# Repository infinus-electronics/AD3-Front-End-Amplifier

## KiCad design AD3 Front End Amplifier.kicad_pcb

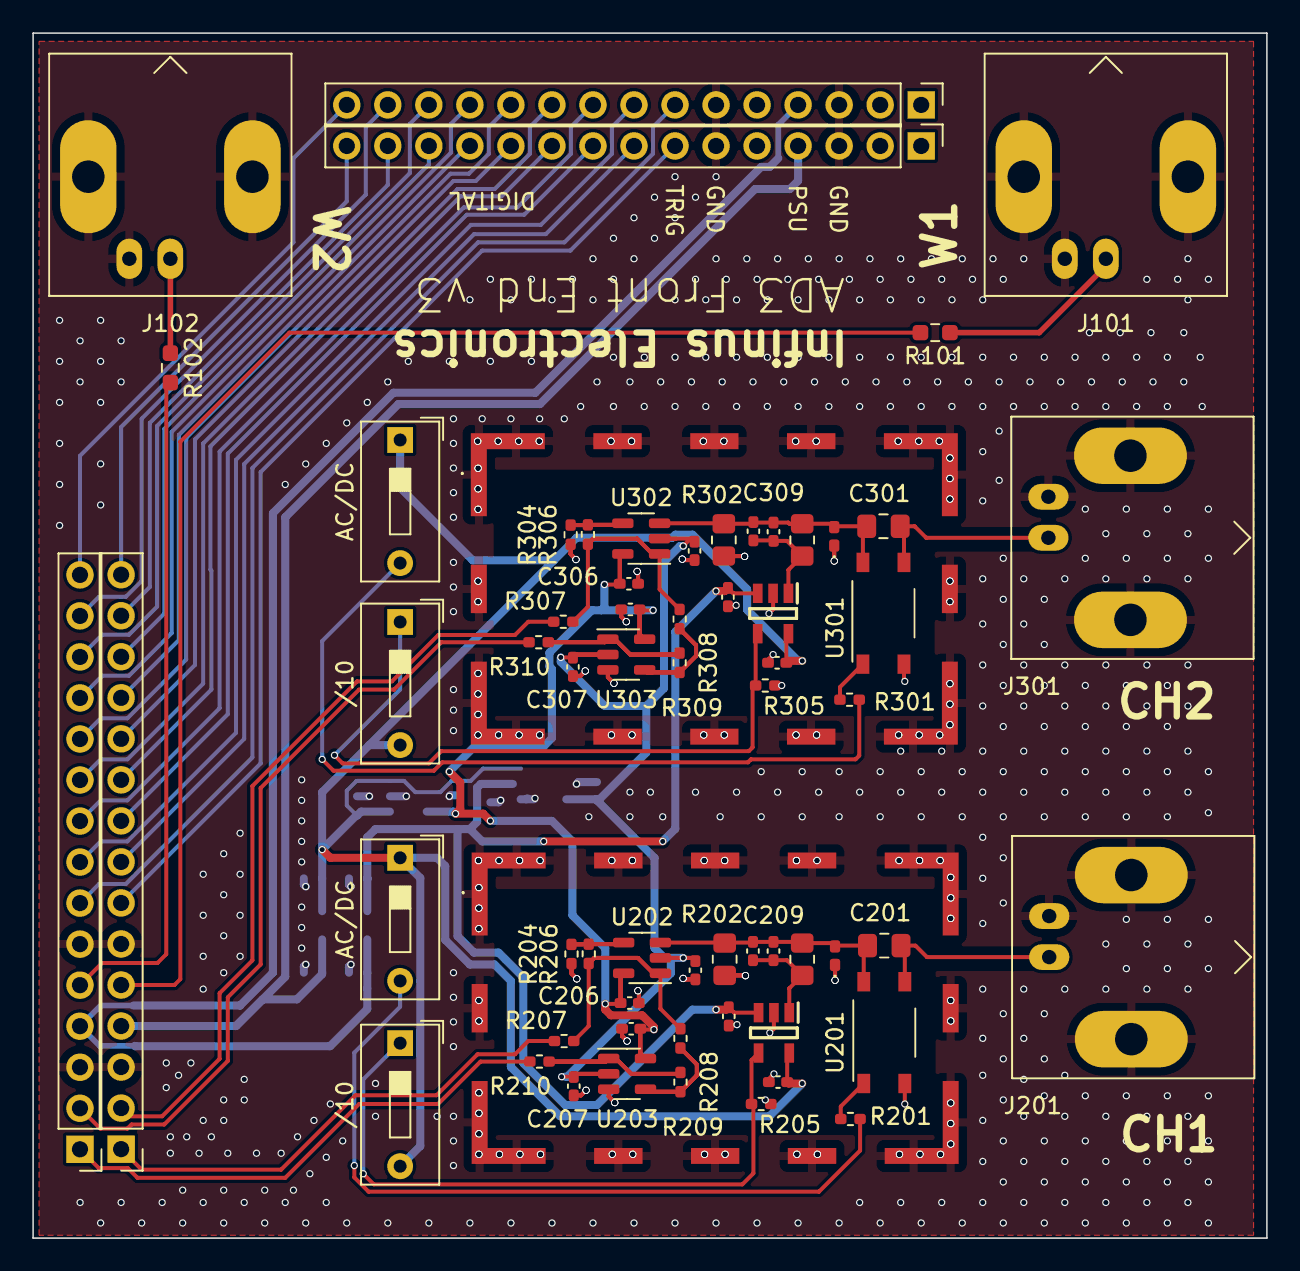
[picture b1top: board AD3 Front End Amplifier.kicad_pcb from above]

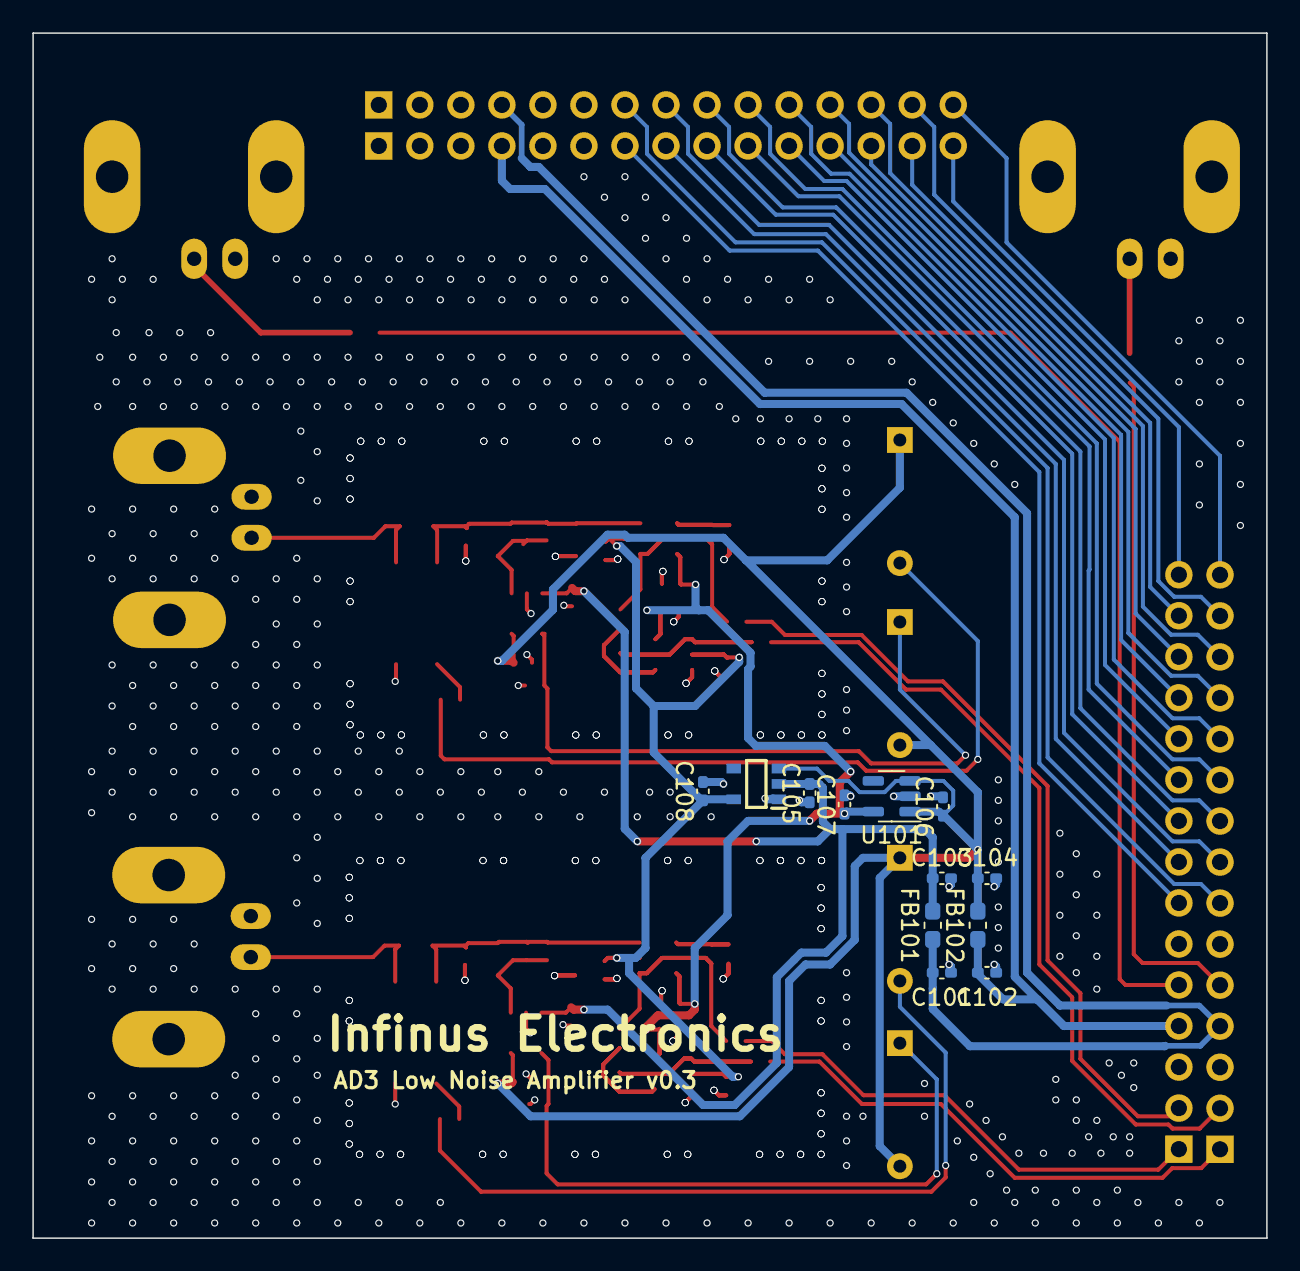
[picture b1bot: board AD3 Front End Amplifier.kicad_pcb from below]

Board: 4 copper layers, 76.4 x 74.6 mm, 76 parts (12 on the bottom side), 53 nets.

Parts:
C101, C102, C103, C104, C105, C106, C107, C108, C203, C204, C205, C206, C207, C208, C303, C304, C305, C306, C307, C308: 1u; C_0402_1005Metric_Pad0.74x0.62mm_HandSolder
C201, C301: 10n; C_0805_2012Metric_Pad1.18x1.45mm_HandSolder
C202, C302: 270p; C_0402_1005Metric_Pad0.74x0.62mm_HandSolder
C209, C309: (select on test); C_0402_1005Metric_Pad0.74x0.62mm_HandSolder
D201, D301: D_TVS; D_0402_1005Metric_Pad0.77x0.64mm_HandSolder
FB101, FB102: FerriteBead_Small; L_0603_1608Metric_Pad1.05x0.95mm_HandSolder
H201, H301: SMS-409F; SMS409F
IC101: XC6901D501MR-G; SOT95P280X130-5N
IC201, IC301: TS12A4516DBVR; SOT95P280X145-5N
J101: W1; BNC_Amphenol_B6252HB-NPP3G-50_Horizontal
J102: W2; BNC_Amphenol_B6252HB-NPP3G-50_Horizontal
J103, J105: Conn_01x15_Pin; PinHeader_1x15_P2.54mm_Vertical
J104, J106: Conn_01x15_Socket; PinHeader_1x15_P2.54mm_Vertical
J201, J301: CH1; BNC_Amphenol_B6252HB-NPP3G-50_Horizontal
R101, R102: 49.9; R_0603_1608Metric_Pad0.98x0.95mm_HandSolder
R201, R206, R208, R209, R301, R306, R308, R309: 402; R_0402_1005Metric_Pad0.72x0.64mm_HandSolder
R202, R302: 1M; R_0805_2012Metric_Pad1.20x1.40mm_HandSolder
R203, R303: 100k; R_0805_2012Metric_Pad1.20x1.40mm_HandSolder
R204, R304: 100; R_0402_1005Metric_Pad0.72x0.64mm_HandSolder
R205, R305: 1k; R_0402_1005Metric_Pad0.72x0.64mm_HandSolder
R207, R210, R307, R310: 22; R_0402_1005Metric_Pad0.72x0.64mm_HandSolder
SW201, SW301: AC/DC; SW_DIP_SPSTx01_Slide_9.78x4.72mm_W7.62mm_P2.54mm
SW202, SW302: /10; SW_DIP_SPSTx01_Slide_9.78x4.72mm_W7.62mm_P2.54mm
U101: MIC5504-2.5YM5; SOT-23-5
U201, U301: TLP176AM; MFSOP6-4_4.4x3.6mm_P1.27mm
U202, U203, U302, U303: OPA356xxDBV; SOT-23-5

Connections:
+2V5: C107.1, C206.1, C208.1, C306.1, C308.1, U101.5 (VOUT), U202.5 (V+), U203.5 (V+), U302.5 (V+), U303.5 (V+)
-2V5: C108.1, C205.1, C207.1, C305.1, C307.1, IC101.5 (-VOUT), U202.2 (V-), U203.2 (V-), U302.2 (V-), U303.2 (V-)
/D0: J105.8, J106.8
/D1: J105.9, J106.9
/D2: J105.10, J106.10
/D3: J105.11, J106.11
/D4: J105.12, J106.12
/D5: J105.13, J106.13
/D6: J105.14, J106.14
/D7: J105.15, J106.15
/D8: J103.8, J104.8
/D9: J103.9, J104.9
/D10: J103.10, J104.10
/D11: J103.11, J104.11
/D12: J103.12, J104.12
/D13: J103.13, J104.13
/D14: J103.14, J104.14
/D15: J103.15, J104.15
/T1: J105.7, J106.7
/T2: J103.7, J104.7
/V+_CONN: C102.1, FB102.1, J105.4, J106.4
/V-_CONN: C101.1, FB101.1, J103.4, J104.4
/W1: J106.5, R101.2
/W2: J104.5, R102.2
CH1_OUT+: J106.1, R207.2
CH1_OUT-: J104.1, R210.2
CH2_OUT+: J106.2, R307.2
CH2_OUT-: J104.2, R310.2
GND: C101.2, C102.2, C103.2, C104.2, C105.1, C106.2, C107.2, C108.2, C203.2, C204.2, C205.2, C206.2, C207.2, C208.2, C303.2, C304.2, C305.2, C306.2, C307.2, C308.2, D201.1 (A1), D301.1 (A1), H201.1, H201.2, H201.3, H201.4, H201.5, H201.6, H201.7, H201.8, H201.9, H201.10, H201.11, H201.12, H201.13, H201.14, H201.15, H201.16, H301.1, H301.2, H301.3, H301.4, H301.5, H301.6, H301.7, H301.8, H301.9, H301.10, H301.11, H301.12, H301.13, H301.14, H301.15, H301.16, IC101.1 (GND), IC201.2 (NO), IC301.2 (NO), J101.2 (Ext), J102.2 (Ext), J103.3, J103.6, J104.3, J104.6, J105.3, J105.6, J106.3, J106.6, J201.2 (Ext), J301.2 (Ext), R202.2, R204.2, R205.2, R302.2, R304.2, R305.2, U101.2 (GND), U201.3, U203.3 (+), U301.3, U303.3 (+)
unnamed: C201.2, C202.1, C209.1, D201.2 (A2), R202.1, R203.1, U201.6, U202.3 (+)
unnamed: C301.2, C302.1, C309.1, D301.2 (A2), R302.1, R303.1, U301.6, U302.3 (+)
unnamed: C202.2, C209.2, IC201.1 (COM), R203.2
unnamed: IC201.4 (IN), R205.1, SW202.1 (A)
unnamed: C302.2, C309.2, IC301.1 (COM), R303.2
unnamed: IC301.4 (IN), R305.1, SW302.1 (A)
unnamed: J101.1 (In), R101.1
unnamed: J102.1 (In), R102.1
unnamed: C201.1, J201.1 (In), U201.4
unnamed: C301.1, J301.1 (In), U301.4
unnamed: R201.1, U201.1
unnamed: R206.2, R207.1, R208.2, U202.1
unnamed: R209.1, R210.1, U203.1
unnamed: R301.1, U301.1
unnamed: R306.2, R307.1, R308.2, U302.1
unnamed: R309.1, R310.1, U303.1
unnamed: R201.2, SW201.2 (B)
unnamed: R301.2, SW301.2 (B)
unnamed: R204.1, R206.1, U202.4 (-)
unnamed: R208.1, R209.2, U203.4 (-)
unnamed: R304.1, R306.1, U302.4 (-)
unnamed: R308.1, R309.2, U303.4 (-)
V+: C104.1, C106.1, C204.1, C304.1, FB102.2, IC101.3 (CE), IC201.5 (V+), IC301.5 (V+), SW201.1 (A), SW202.2 (B), SW301.1 (A), SW302.2 (B), U101.1 (VIN), U101.3 (EN)
V-: C103.1, C105.2, C203.1, C303.1, FB101.2, IC101.2 (-VIN), IC201.3 (V-), IC301.3 (V-)

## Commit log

2023-11-05 v1 commit
2023-11-05 pdf schematics
2023-12-17 v2 gerbers and pdf schematics
2023-12-17 v3 initial schematic
2023-12-17 changed mux
2023-12-17 Ch1 Layout
2023-12-18 v3 done
2023-12-18 mk2 svgs
2023-12-19 mux in mistake fix
